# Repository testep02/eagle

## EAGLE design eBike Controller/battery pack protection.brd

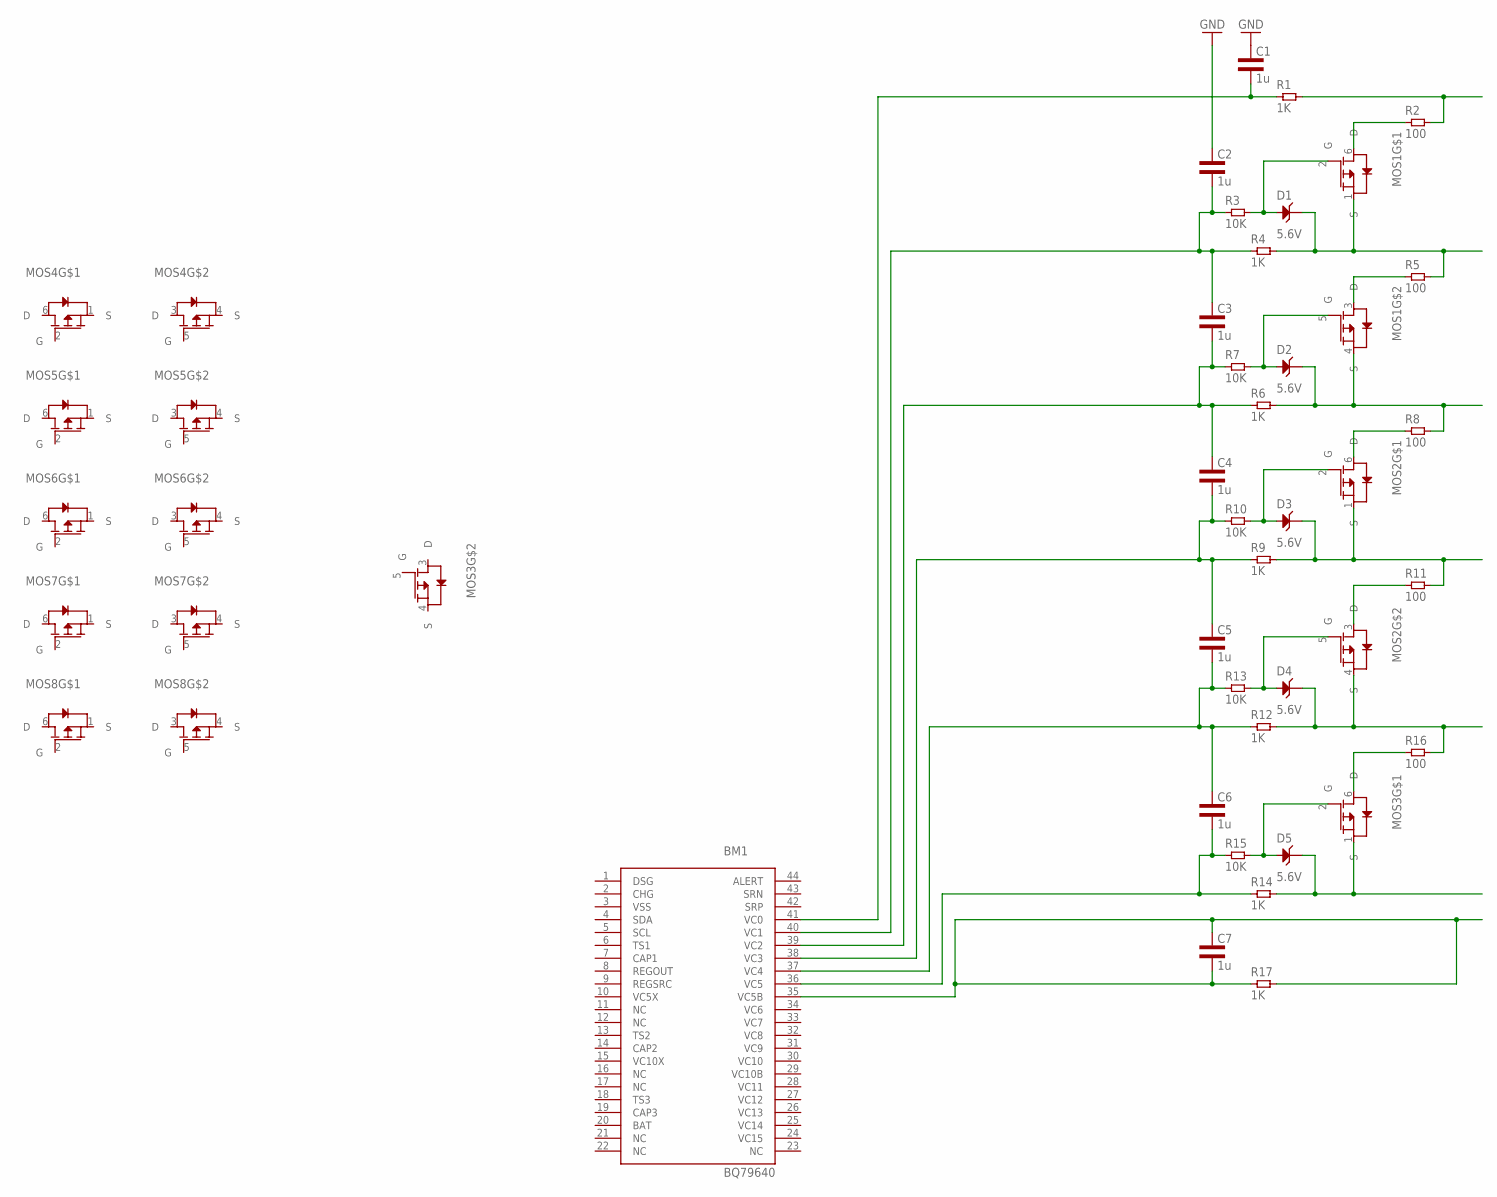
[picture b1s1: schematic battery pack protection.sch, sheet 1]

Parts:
BM1: BQ76940; R-PDSO-G44
C1, C2, C3, C4, C5, C6, C7: 1u; 0805L3
D1, D2, D3, D4, D5: 5.6V; SOD323
MOS1, MOS2, MOS3, MOS4, MOS5, MOS6, MOS7, MOS8: FDY1002PZ; SC89-6
R1, R4, R6, R9, R12, R14, R17: 1K; 0805L3
R2, R5, R8, R11, R16: 100; 1206L3
R3, R7, R10, R13, R15: 10K; 0805L3

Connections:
GND: C1.1, C2.1
unnamed: BM1.41 (VC0), C1.2, R1.1
unnamed: R1.2, R2.2
unnamed: MOS1.6 (D), R2.1
unnamed: D1.1 (ANODE), MOS1.2 (G), R3.2
unnamed: D1.2 (CATHODE), MOS1.1 (S), R4.2, R5.2
unnamed: BM1.40 (VC1), C2.2, C3.1, R3.1, R4.1
unnamed: D2.1 (ANODE), MOS1.5 (G), R7.2
unnamed: BM1.39 (VC2), C3.2, C4.1, R6.1, R7.1
unnamed: D2.2 (CATHODE), MOS1.4 (S), R6.2, R8.2
unnamed: MOS1.3 (D), R5.1
unnamed: BM1.38 (VC3), C4.2, C5.1, R9.1, R10.1
unnamed: D3.1 (ANODE), MOS2.2 (G), R10.2
unnamed: D3.2 (CATHODE), MOS2.1 (S), R9.2, R11.2
unnamed: MOS2.6 (D), R8.1
unnamed: BM1.37 (VC4), C5.2, C6.1, R12.1, R13.1
unnamed: D4.2 (CATHODE), MOS2.4 (S), R12.2, R16.2
unnamed: D4.1 (ANODE), MOS2.5 (G), R13.2
unnamed: MOS2.3 (D), R11.1
unnamed: BM1.36 (VC5), C6.2, R14.1, R15.1
unnamed: D5.2 (CATHODE), MOS3.1 (S), R14.2
unnamed: MOS3.6 (D), R16.1
unnamed: D5.1 (ANODE), MOS3.2 (G), R15.2
unnamed: BM1.35 (VC5B), C7.1, C7.2, R17.1, R17.2

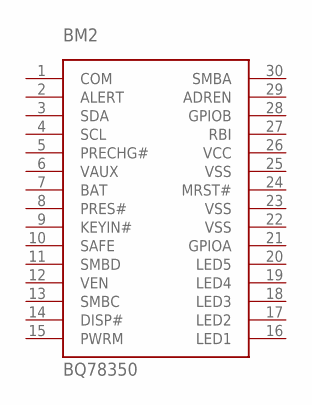
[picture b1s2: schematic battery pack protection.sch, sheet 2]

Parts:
BM2: BQ78350; R-PDSO-G30

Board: 4 copper layers, 39 parts (0 on the bottom side), 24 nets, no tracks yet.

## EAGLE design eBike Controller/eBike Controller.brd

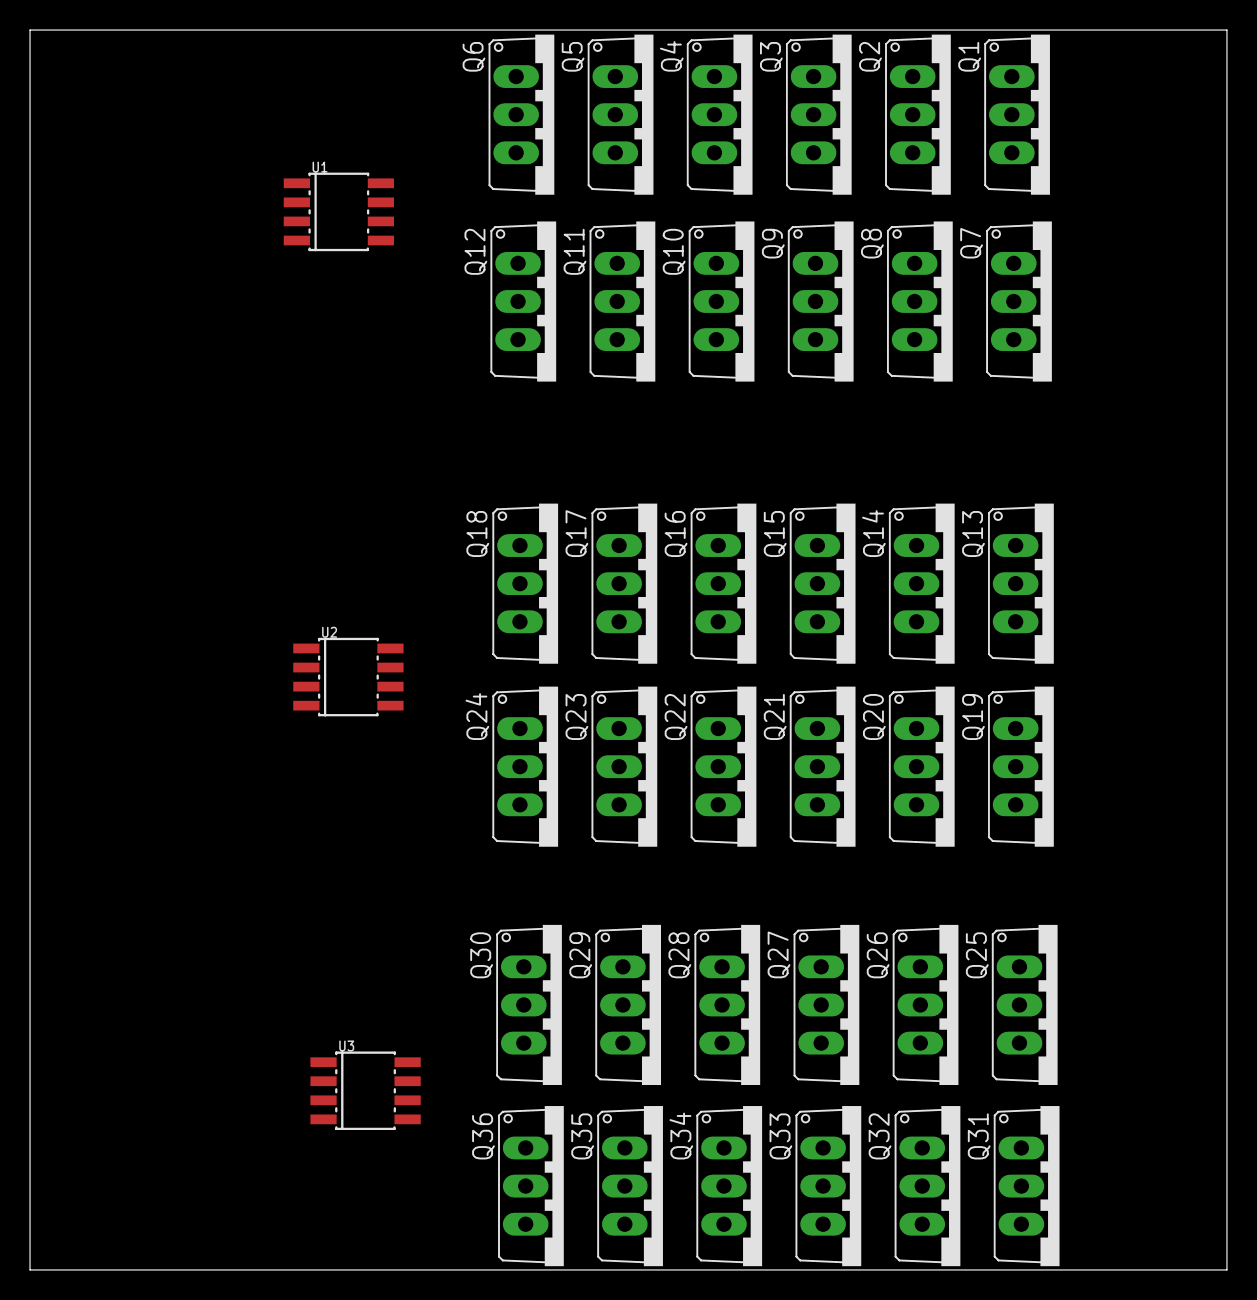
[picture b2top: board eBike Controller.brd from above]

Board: 2 copper layers, 79.7 x 82.6 mm, 39 parts (0 on the bottom side), 13 nets, no tracks yet.

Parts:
Q1, Q2, Q3, Q4, Q5, Q6, Q7, Q8, Q9, Q10, Q11, Q12, Q13, Q14, Q15, Q16, Q17, Q18, Q19, Q20, Q21, Q22, Q23, Q24, Q25, Q26, Q27, Q28, Q29, Q30, Q31, Q32, Q33, Q34, Q35, Q36: TO220V
U1, U2, U3: OPEN-BLDC_BD_IR2101; OPEN-BLDC_SO8

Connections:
BAT+: Q1.2, Q2.2, Q3.2, Q4.2, Q5.2, Q6.2, Q13.2, Q14.2, Q15.2, Q16.2, Q17.2, Q18.2, Q25.2, Q26.2, Q27.2, Q28.2, Q29.2, Q30.2
unnamed: Q1.3, Q2.3, Q3.3, Q4.3, Q5.3, Q6.3, Q7.2, Q8.2, Q9.2, Q10.2, Q11.2, Q12.2
unnamed: Q7.3, Q8.3, Q9.3, Q10.3, Q11.3, Q12.3
unnamed: Q7.1, Q8.1, Q9.1, Q10.1, Q11.1, Q12.1, U1.5
unnamed: Q1.1, Q2.1, Q3.1, Q4.1, Q5.1, Q6.1, U1.7
unnamed: Q13.3, Q14.3, Q15.3, Q16.3, Q17.3, Q18.3, Q19.2, Q20.2, Q21.2, Q22.2, Q23.2, Q24.2
unnamed: Q13.1, Q14.1, Q15.1, Q16.1, Q17.1, Q18.1, U2.7
unnamed: Q19.1, Q20.1, Q21.1, Q22.1, Q23.1, Q24.1, U2.5
unnamed: Q25.1, Q26.1, Q27.1, Q28.1, Q29.1, Q30.1, U3.7
unnamed: Q31.1, Q32.1, Q33.1, Q34.1, Q35.1, Q36.1, U3.5
unnamed: Q19.3, Q20.3, Q21.3, Q22.3, Q23.3, Q24.3
unnamed: Q25.3, Q26.3, Q27.3, Q28.3, Q29.3, Q30.3, Q31.2, Q32.2, Q33.2, Q34.2, Q35.2, Q36.2
unnamed: Q31.3, Q32.3, Q33.3, Q34.3, Q35.3, Q36.3

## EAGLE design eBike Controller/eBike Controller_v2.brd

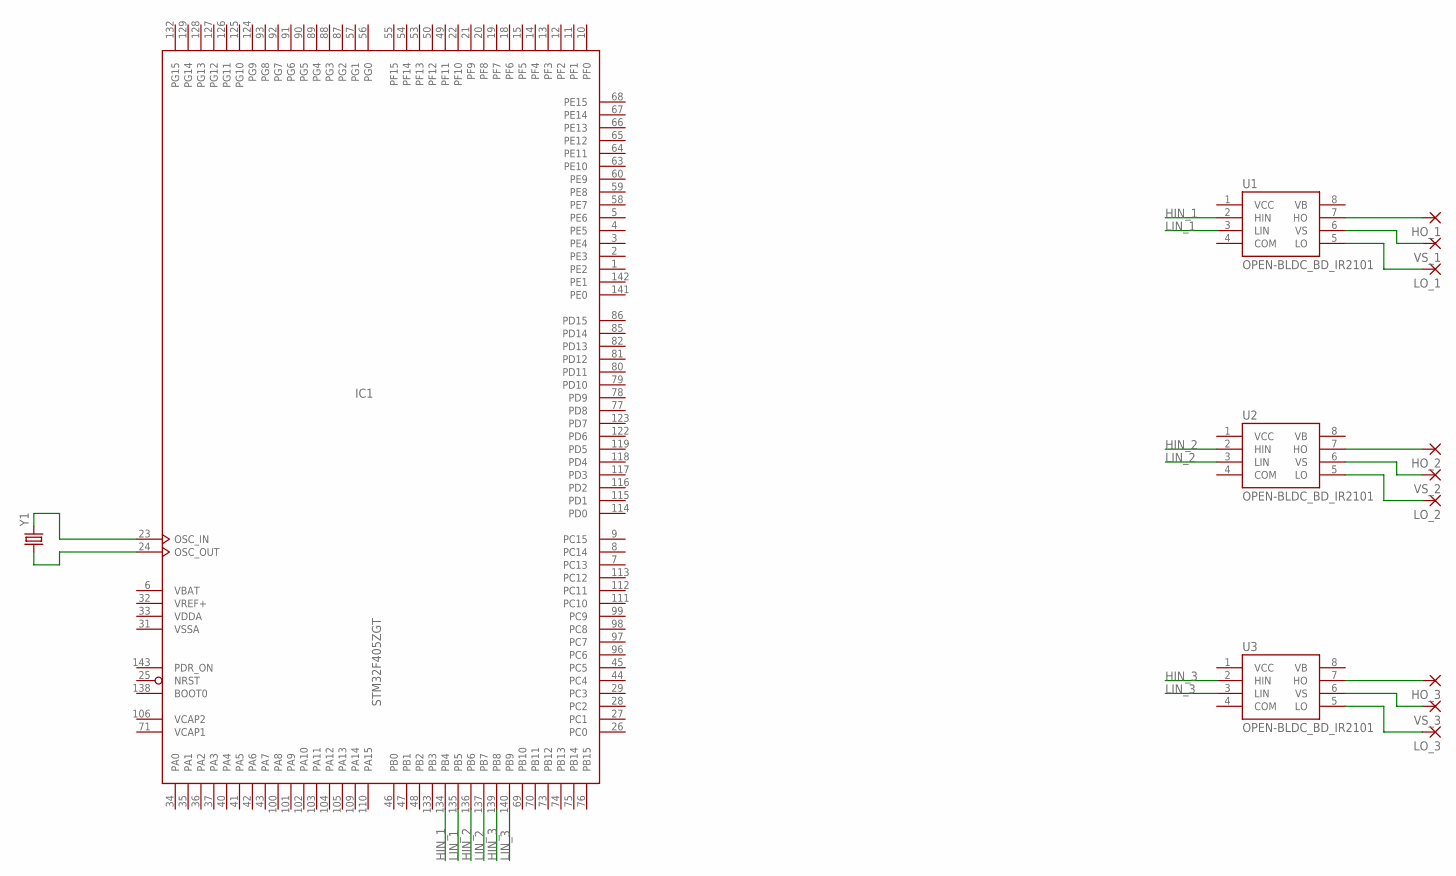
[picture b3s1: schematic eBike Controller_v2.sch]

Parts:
HO_1, HO_2, HO_3: 3,81/1,4
IC1: STM32F405ZGT; LQFP144
LO_1, LO_2, LO_3: 3,81/1,4
U1, U2, U3: OPEN-BLDC_BD_IR2101; OPEN-BLDC_SO8
VS_1, VS_2, VS_3: 3,81/1,4
Y1: CRYSTALHC49US; HC49US

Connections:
HIN_1: IC1.134 (PB4), U1.2 (HIN)
HIN_2: IC1.136 (PB6), U2.2 (HIN)
HIN_3: IC1.139 (PB8), U3.2 (HIN)
HO_1: HO_1.1, U1.7 (HO)
HO_2: HO_2.1, U2.7 (HO)
HO_3: HO_3.1, U3.7 (HO)
LIN_1: IC1.135 (PB5), U1.3 (LIN)
LIN_2: IC1.137 (PB7), U2.3 (LIN)
LIN_3: IC1.140 (PB9), U3.3 (LIN)
LO_1: LO_1.1, U1.5 (LO)
LO_2: LO_2.1, U2.5 (LO)
LO_3: LO_3.1, U3.5 (LO)
unnamed: IC1.24 (OSC_OUT), Y1.1
unnamed: IC1.23 (OSC_IN), Y1.2
VBAT: IC1.6 (VBAT)
VCAP1: IC1.71 (VCAP1)
VCAP2: IC1.106 (VCAP2)
VDD: IC1.17 (VDD), IC1.30 (VDD), IC1.39 (VDD), IC1.52 (VDD), IC1.62 (VDD), IC1.72 (VDD), IC1.84 (VDD), IC1.95 (VDD), IC1.108 (VDD), IC1.121 (VDD), IC1.131 (VDD), IC1.144 (VDD)
VDDA: IC1.33 (VDDA)
VREF+: IC1.32 (VREF+)
VSS: IC1.16 (VSS), IC1.38 (VSS), IC1.51 (VSS), IC1.61 (VSS), IC1.83 (VSS), IC1.94 (VSS), IC1.107 (VSS), IC1.120 (VSS), IC1.130 (VSS)
VSSA: IC1.31 (VSSA)
VS_1: U1.6 (VS), VS_1.1
VS_2: U2.6 (VS), VS_2.1
VS_3: U3.6 (VS), VS_3.1

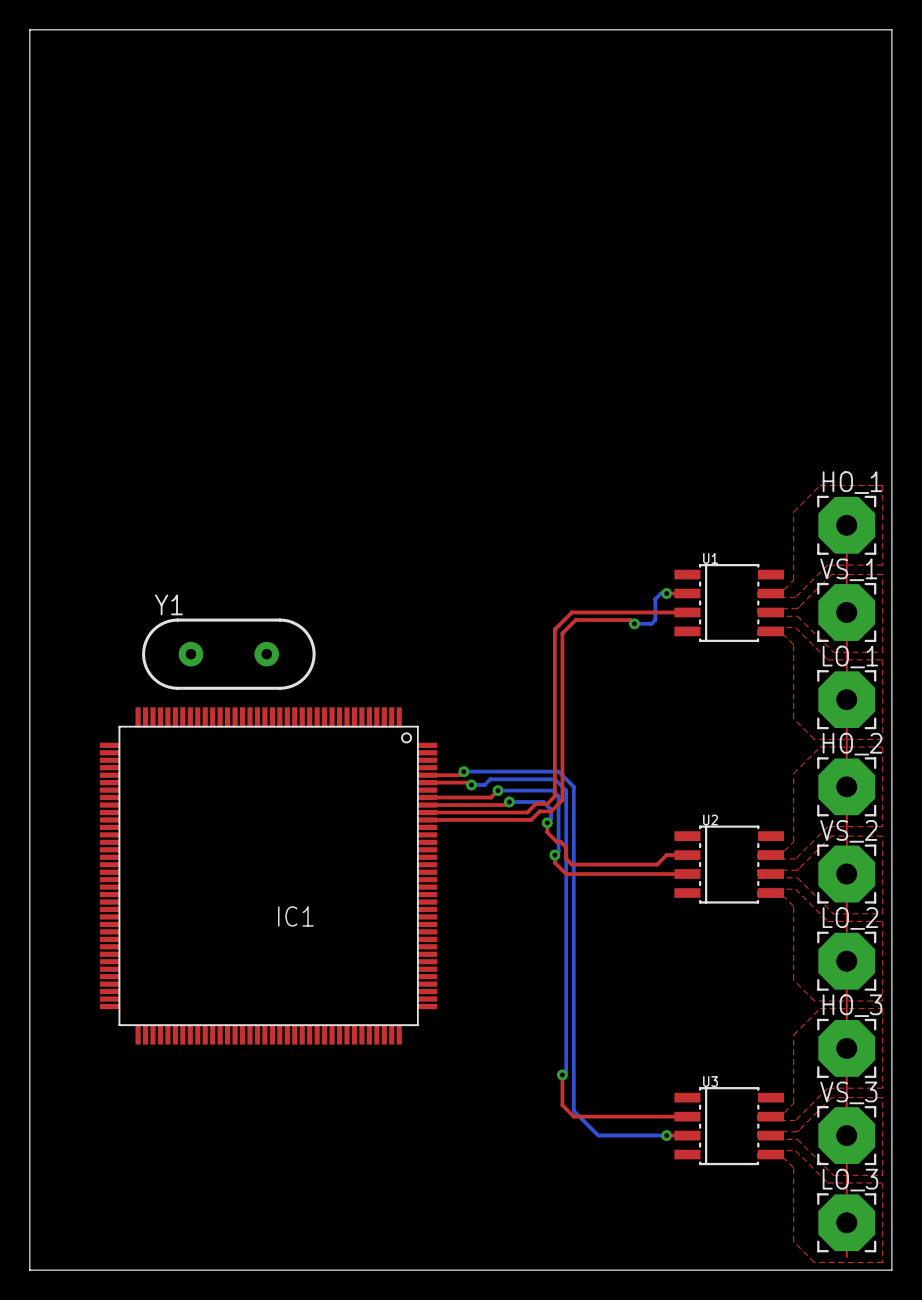
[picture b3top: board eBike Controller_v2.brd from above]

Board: 2 copper layers, 57.8 x 83.1 mm, 14 parts (0 on the bottom side), 19 nets.

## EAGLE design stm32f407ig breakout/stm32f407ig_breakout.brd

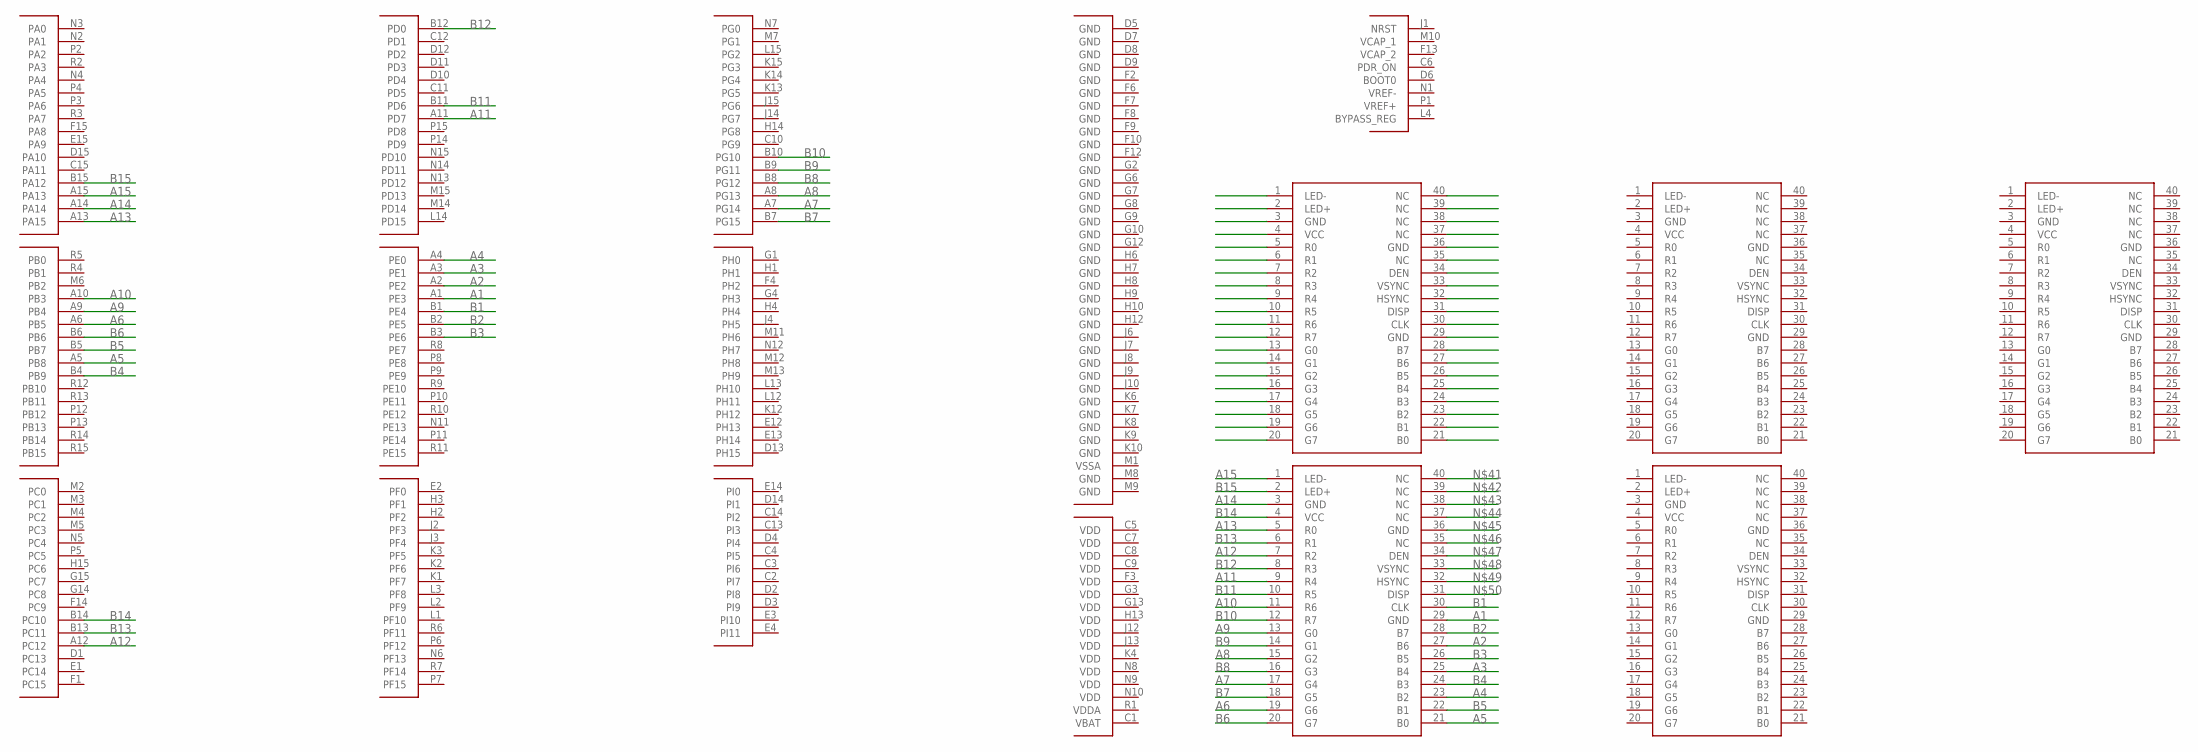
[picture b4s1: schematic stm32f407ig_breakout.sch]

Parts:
TFT1, TFT2, TFT3, TFT4, TFT5: MOLEX_CONNECTORS_SMD_NHD-4.3-480272EF-ATXL; MOLEX_CONNECTORS_SMD_40-PIN_SMD
U$1: STM32F407IG; UFBGA176+25

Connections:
A1: TFT4.29 (GND), U$1.A1 (PE3)
A2: TFT4.27 (B6), U$1.A2 (PE2)
A3: TFT4.25 (B4), U$1.A3 (PE1)
A4: TFT4.23 (B2), U$1.A4 (PE0)
A5: TFT4.21 (B0), U$1.A5 (PB8)
A6: TFT4.19 (G6), U$1.A6 (PB5)
A7: TFT4.17 (G4), U$1.A7 (PG14)
A8: TFT4.15 (G2), U$1.A8 (PG13)
A9: TFT4.13 (G0), U$1.A9 (PB4)
A10: TFT4.11 (R6), U$1.A10 (PB3)
A11: TFT4.9 (R4), U$1.A11 (PD7)
A12: TFT4.7 (R2), U$1.A12 (PC12)
A13: TFT4.5 (R0), U$1.A13 (PA15)
A14: TFT4.3 (GND), U$1.A14
A15: TFT4.1 (LED-), U$1.A15 (PA13)
B1: TFT4.30 (CLK), U$1.B1 (PE4)
B2: TFT4.28 (B7), U$1.B2 (PE5)
B3: TFT4.26 (B5), U$1.B3 (PE6)
B4: TFT4.24 (B3), U$1.B4 (PB9)
B5: TFT4.22 (B1), U$1.B5 (PB7)
B6: TFT4.20 (G7), U$1.B6
B7: TFT4.18 (G5), U$1.B7 (PG15)
B8: TFT4.16 (G3), U$1.B8 (PG12)
B9: TFT4.14 (G1), U$1.B9 (PG11)
B10: TFT4.12 (R7), U$1.B10 (PG10)
B11: TFT4.10 (R5), U$1.B11 (PD6)
B12: TFT4.8 (R3), U$1.B12 (PD0)
B13: TFT4.6 (R1), U$1.B13 (PC11)
B14: TFT4.4 (VCC), U$1.B14 (PC10)
B15: TFT4.2 (LED+), U$1.B15 (PA12)

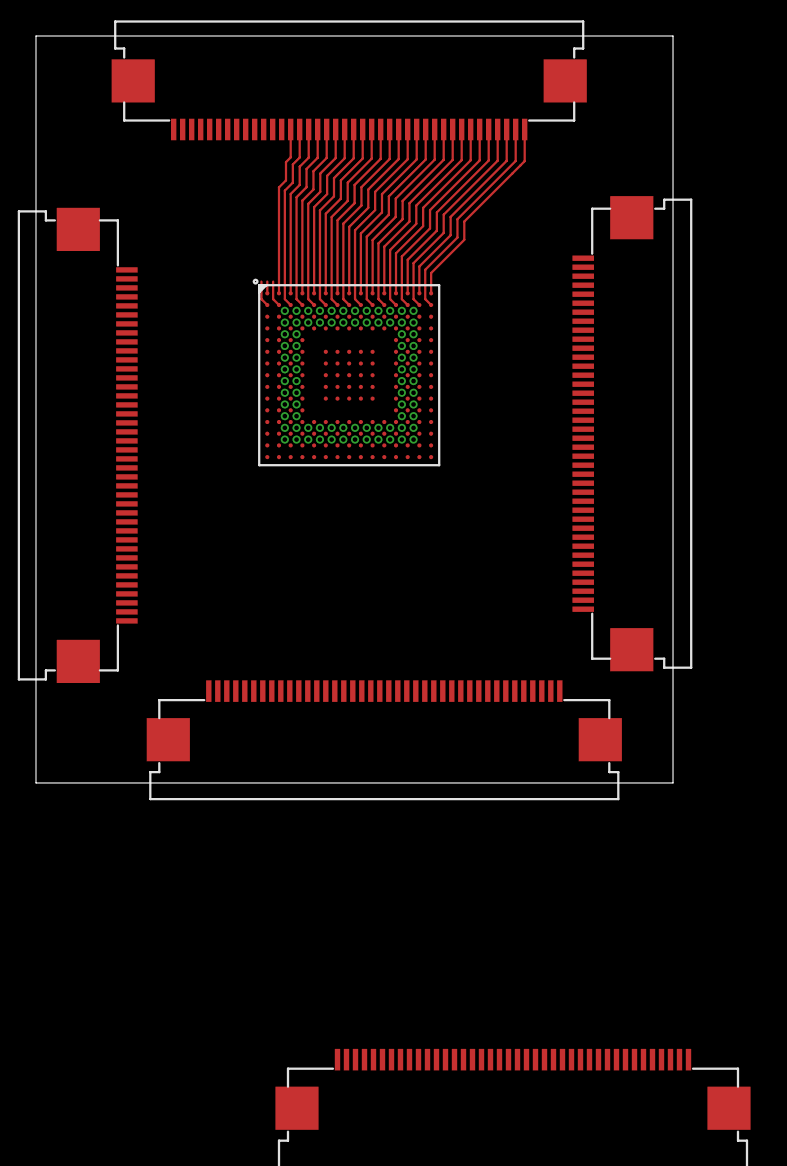
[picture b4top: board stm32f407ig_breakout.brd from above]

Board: 2 copper layers, 35.4 x 41.5 mm, 6 parts (0 on the bottom side), 30 nets.

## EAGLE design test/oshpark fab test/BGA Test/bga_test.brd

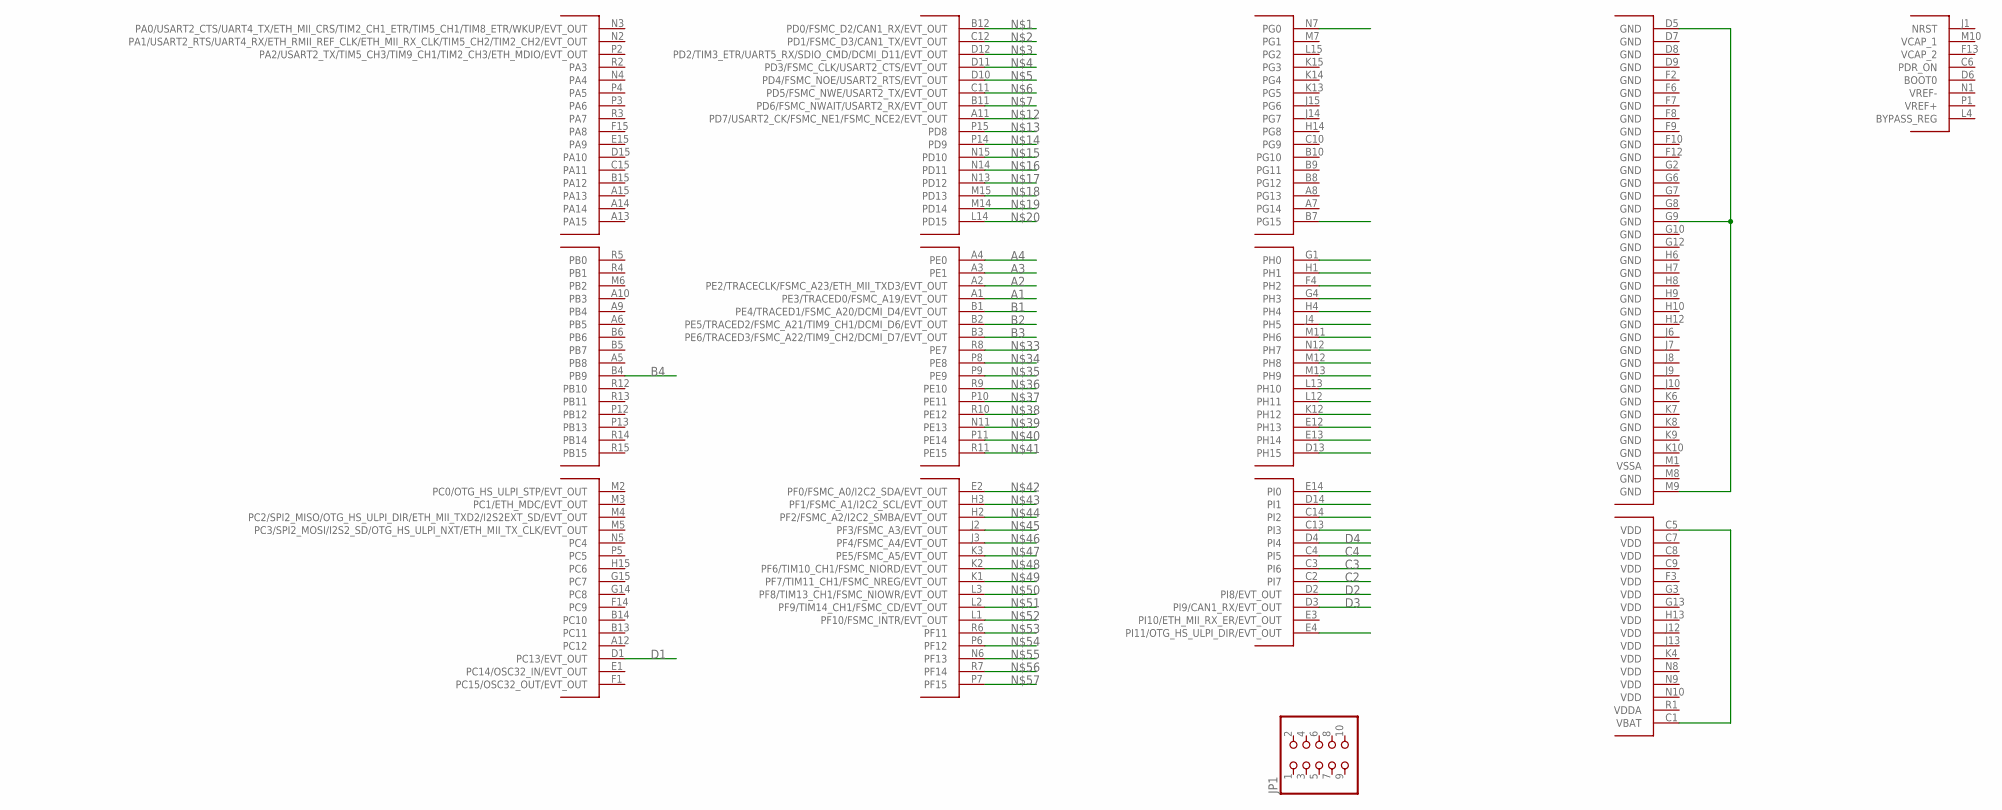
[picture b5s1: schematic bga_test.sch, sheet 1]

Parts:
JP1: PINHD-2X5; 2X05
U$1: STM32_32BIT_MCU_STM32F407IG; STM32_32BIT_MCU_UFBGA176+25

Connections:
A1: U$1.A1 (PE3/TRACED0/FSMC_A19/EVT_OUT); also elsewhere on the board
A2: U$1.A2 (PE2/TRACECLK/FSMC_A23/ETH_MII_TXD3/EVT_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); also elsewhere on the board
A3: U$1.A3 (PE1); also elsewhere on the board
A4: U$1.A4 (PE0); also elsewhere on the board
B1: U$1.B1 (PE4/TRACED1/FSMC_A20/DCMI_D4/EVT_OUT); also elsewhere on the board
B2: U$1.B2 (PE5/TRACED2/FSMC_A21/TIM9_CH1/DCMI_D6/E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); also elsewhere on the board
B3: U$1.B3 (PE6/TRACED3/FSMC_A22/TIM9_CH2/DCMI_D7/E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); also elsewhere on the board
B4: U$1.B4 (PB9); also elsewhere on the board
C2: U$1.C2 (PI7); also elsewhere on the board
C3: U$1.C3 (PI6); also elsewhere on the board
C4: U$1.C4 (PI5); also elsewhere on the board
D1: U$1.D1 (PC13/EVT_OUT)
D2: U$1.D2 (PI8/EVT_OUT); also elsewhere on the board
D3: U$1.D3 (PI9/CAN1_RX/EVT_OUT); also elsewhere on the board
D4: U$1.D4 (PI4); also elsewhere on the board
unnamed: U$1.D5 (GND), U$1.G9 (GND), U$1.M9 (GND)
unnamed: U$1.C1 (VBAT), U$1.C5 (VDD)

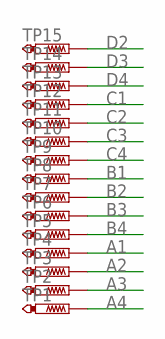
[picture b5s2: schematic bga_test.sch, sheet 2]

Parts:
TP1, TP2, TP3, TP4, TP5, TP6, TP7, TP8, TP9, TP10, TP11, TP12, TP13, TP14, TP15: PTR1TP06R; TP06R

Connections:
A1: TP4.TP; also elsewhere on the board
A2: TP3.TP; also elsewhere on the board
A3: TP2.TP; also elsewhere on the board
A4: TP1.TP; also elsewhere on the board
B1: TP8.TP; also elsewhere on the board
B2: TP7.TP; also elsewhere on the board
B3: TP6.TP; also elsewhere on the board
B4: TP5.TP; also elsewhere on the board
C1: TP12.TP
C2: TP11.TP; also elsewhere on the board
C3: TP10.TP; also elsewhere on the board
C4: TP9.TP; also elsewhere on the board
D2: TP15.TP; also elsewhere on the board
D3: TP14.TP; also elsewhere on the board
D4: TP13.TP; also elsewhere on the board

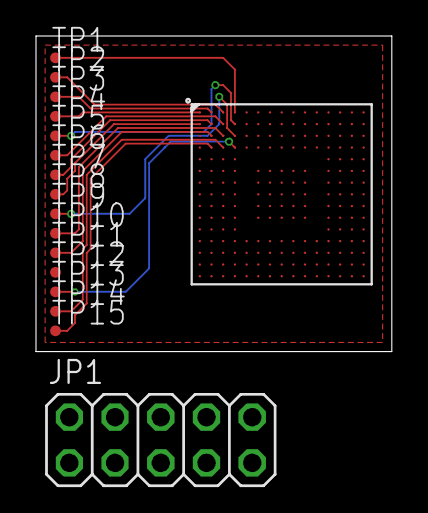
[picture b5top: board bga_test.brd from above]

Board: 4 copper layers, 19.8 x 17.5 mm, 17 parts (0 on the bottom side), 16 nets.

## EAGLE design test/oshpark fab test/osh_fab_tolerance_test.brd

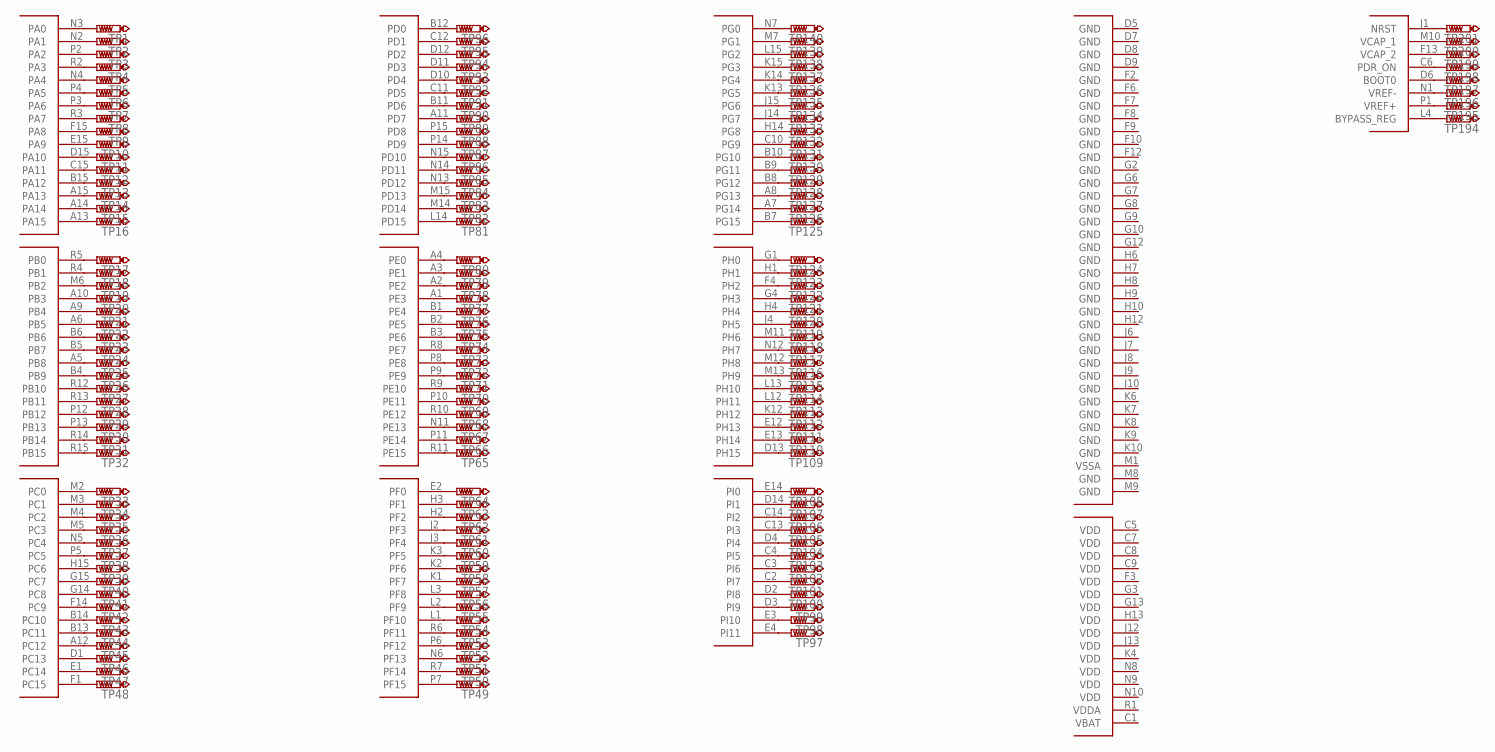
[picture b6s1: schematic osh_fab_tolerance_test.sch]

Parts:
TP1, TP2, TP3, TP4, TP5, TP6, TP7, TP8, TP9, TP10, TP11, TP12, TP13, TP14, TP15, TP16, TP17, TP18, TP19, TP20, TP21, TP22, TP23, TP24, TP25, TP26, TP27, TP28, TP29, TP30, TP31, TP32, TP33, TP34, TP35, TP36, TP37, TP38, TP39, TP40, TP41, TP42, TP43, TP44, TP45, TP46, TP47, TP48, TP49, TP50, TP51, TP52, TP53, TP54, TP55, TP56, TP57, TP58, TP59, TP60, TP61, TP62, TP63, TP64, TP65, TP66, TP67, TP68, TP69, TP70, TP71, TP72, TP73, TP74, TP75, TP76, TP77, TP78, TP79, TP80, TP81, TP82, TP83, TP84, TP85, TP86, TP87, TP88, TP89, TP90, TP91, TP92, TP93, TP94, TP95, TP96, TP97, TP98, TP99, TP100, TP101, TP102, TP103, TP104, TP105, TP106, TP107, TP108, TP109, TP110, TP111, TP112, TP113, TP114, TP115, TP116, TP117, TP118, TP119, TP120, TP121, TP122, TP123, TP124, TP125, TP126, TP127, TP128, TP129, TP130, TP131, TP132, TP133, TP134, TP135, TP136, TP137, TP138, TP139, TP140, TP194, TP195, TP196, TP197, TP198, TP199, TP200, TP201: PTR1TP09R; TP09R
U$1: STM32_32BIT_MCU_STM32F407IG; STM32_32BIT_MCU_UFBGA176+25

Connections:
unnamed: TP1.TP, U$1.N3 (PA0)
unnamed: TP2.TP, U$1.N2 (PA1)
unnamed: TP3.TP, U$1.P2 (PA2)
unnamed: TP4.TP, U$1.R2 (PA3)
unnamed: TP5.TP, U$1.N4 (PA4)
unnamed: TP6.TP, U$1.P4 (PA5)
unnamed: TP7.TP, U$1.P3 (PA6)
unnamed: TP8.TP, U$1.R3 (PA7)
unnamed: TP9.TP, U$1.F15 (PA8)
unnamed: TP10.TP, U$1.E15 (PA9)
unnamed: TP11.TP, U$1.D15 (PA10)
unnamed: TP12.TP, U$1.C15 (PA11)
unnamed: TP13.TP, U$1.B15 (PA12)
unnamed: TP14.TP, U$1.A15 (PA13)
unnamed: TP15.TP, U$1.A14
unnamed: TP16.TP, U$1.A13 (PA15)
unnamed: TP17.TP, U$1.R5 (PB0)
unnamed: TP18.TP, U$1.R4 (PB1)
unnamed: TP19.TP, U$1.M6 (PB2)
unnamed: TP20.TP, U$1.A10 (PB3)
unnamed: TP21.TP, U$1.A9 (PB4)
unnamed: TP22.TP, U$1.A6 (PB5)
unnamed: TP23.TP, U$1.B6
unnamed: TP24.TP, U$1.B5 (PB7)
unnamed: TP25.TP, U$1.A5 (PB8)
unnamed: TP26.TP, U$1.B4 (PB9)
unnamed: TP27.TP, U$1.R12 (PB10)
unnamed: TP28.TP, U$1.R13 (PB11)
unnamed: TP29.TP, U$1.P12 (PB12)
unnamed: TP30.TP, U$1.P13 (PB13)
unnamed: TP31.TP, U$1.R14 (PB14)
unnamed: TP32.TP, U$1.R15 (PB15)
unnamed: TP33.TP, U$1.M2 (PC0)
unnamed: TP34.TP, U$1.M3 (PC1)
unnamed: TP35.TP, U$1.M4 (PC2)
unnamed: TP36.TP, U$1.M5 (PC3)
unnamed: TP37.TP, U$1.N5 (PC4)
unnamed: TP38.TP, U$1.P5 (PC5)
unnamed: TP39.TP, U$1.H15 (PC6)
unnamed: TP40.TP, U$1.G15 (PC7)
unnamed: TP41.TP, U$1.G14 (PC8)
unnamed: TP42.TP, U$1.F14 (PC9)
unnamed: TP43.TP, U$1.B14 (PC10)
unnamed: TP44.TP, U$1.B13 (PC11)
unnamed: TP45.TP, U$1.A12 (PC12)
unnamed: TP46.TP, U$1.D1 (PC13)
unnamed: TP47.TP, U$1.E1 (PC14)
unnamed: TP48.TP, U$1.F1 (PC15)
unnamed: TP49.TP, U$1.P7 (PF15)
unnamed: TP50.TP, U$1.R7 (PF14)
unnamed: TP51.TP, U$1.N6 (PF13)
unnamed: TP52.TP, U$1.P6 (PF12)
unnamed: TP53.TP, U$1.R6 (PF11)
unnamed: TP54.TP, U$1.L1 (PF10)
unnamed: TP55.TP, U$1.L2 (PF9)
unnamed: TP56.TP, U$1.L3 (PF8)
unnamed: TP57.TP, U$1.K1 (PF7)
unnamed: TP58.TP, U$1.K2 (PF6)
unnamed: TP59.TP, U$1.K3 (PF5)
unnamed: TP60.TP, U$1.J3 (PF4)
unnamed: TP61.TP, U$1.J2 (PF3)
unnamed: TP62.TP, U$1.H2 (PF2)
unnamed: TP63.TP, U$1.H3 (PF1)
unnamed: TP64.TP, U$1.E2 (PF0)
unnamed: TP65.TP, U$1.R11 (PE15)
unnamed: TP66.TP, U$1.P11 (PE14)
unnamed: TP67.TP, U$1.N11 (PE13)
unnamed: TP68.TP, U$1.R10 (PE12)
unnamed: TP69.TP, U$1.P10 (PE11)
unnamed: TP70.TP, U$1.R9 (PE10)
unnamed: TP71.TP, U$1.P9 (PE9)
unnamed: TP72.TP, U$1.P8 (PE8)
unnamed: TP73.TP, U$1.R8 (PE7)
unnamed: TP74.TP, U$1.B3 (PE6)
unnamed: TP75.TP, U$1.B2 (PE5)
unnamed: TP76.TP, U$1.B1 (PE4)
unnamed: TP77.TP, U$1.A1 (PE3)
unnamed: TP78.TP, U$1.A2 (PE2)
unnamed: TP79.TP, U$1.A3 (PE1)
unnamed: TP80.TP, U$1.A4 (PE0)
unnamed: TP81.TP, U$1.L14 (PD15)
unnamed: TP82.TP, U$1.M14 (PD14)
unnamed: TP83.TP, U$1.M15 (PD13)
unnamed: TP84.TP, U$1.N13 (PD12)
unnamed: TP85.TP, U$1.N14 (PD11)
unnamed: TP86.TP, U$1.N15 (PD10)
unnamed: TP87.TP, U$1.P14 (PD9)
unnamed: TP88.TP, U$1.P15 (PD8)
unnamed: TP89.TP, U$1.A11 (PD7)
unnamed: TP90.TP, U$1.B11 (PD6)
unnamed: TP91.TP, U$1.C11 (PD5)
unnamed: TP92.TP, U$1.D10 (PD4)
unnamed: TP93.TP, U$1.D11 (PD3)
unnamed: TP94.TP, U$1.D12 (PD2)
unnamed: TP95.TP, U$1.C12 (PD1)
unnamed: TP96.TP, U$1.B12 (PD0)
unnamed: TP97.TP, U$1.E4 (PI11)
unnamed: TP98.TP, U$1.E3 (PI10)
unnamed: TP99.TP, U$1.D3 (PI9)
unnamed: TP100.TP, U$1.D2 (PI8)
unnamed: TP101.TP, U$1.C2 (PI7)
unnamed: TP102.TP, U$1.C3 (PI6)
unnamed: TP103.TP, U$1.C4 (PI5)
unnamed: TP104.TP, U$1.D4 (PI4)
unnamed: TP105.TP, U$1.C13 (PI3)
unnamed: TP106.TP, U$1.C14 (PI2)
unnamed: TP107.TP, U$1.D14 (PI1)
unnamed: TP108.TP, U$1.E14 (PI0)
unnamed: TP109.TP, U$1.D13 (PH15)
unnamed: TP110.TP, U$1.E13 (PH14)
unnamed: TP111.TP, U$1.E12 (PH13)
unnamed: TP112.TP, U$1.K12 (PH12)
unnamed: TP113.TP, U$1.L12 (PH11)
unnamed: TP114.TP, U$1.L13 (PH10)
unnamed: TP115.TP, U$1.M13 (PH9)
unnamed: TP116.TP, U$1.M12 (PH8)
unnamed: TP117.TP, U$1.N12 (PH7)
unnamed: TP118.TP, U$1.M11 (PH6)
unnamed: TP119.TP, U$1.J4 (PH5)
unnamed: TP120.TP, U$1.H4
unnamed: TP121.TP, U$1.G4 (PH3)
unnamed: TP122.TP, U$1.F4 (PH2)
unnamed: TP123.TP, U$1.H1
unnamed: TP124.TP, U$1.G1 (PH0)
unnamed: TP125.TP, U$1.B7 (PG15)
unnamed: TP126.TP, U$1.A7 (PG14)
unnamed: TP127.TP, U$1.A8 (PG13)
unnamed: TP128.TP, U$1.B8 (PG12)
unnamed: TP129.TP, U$1.B9 (PG11)
unnamed: TP130.TP, U$1.B10 (PG10)
unnamed: TP131.TP, U$1.C10 (PG9)
unnamed: TP132.TP, U$1.H14 (PG8)
unnamed: TP133.TP, U$1.J14 (PG7)
unnamed: TP134.TP, U$1.J15 (PG6)
unnamed: TP135.TP, U$1.K13 (PG5)
unnamed: TP136.TP, U$1.K14 (PG4)
unnamed: TP137.TP, U$1.K15 (PG3)
unnamed: TP138.TP, U$1.L15 (PG2)
unnamed: TP139.TP, U$1.M7 (PG1)
unnamed: TP140.TP, U$1.N7 (PG0)
unnamed: TP194.TP, U$1.L4 (BYPASS_REG)
unnamed: TP195.TP, U$1.P1 (VREF+)
unnamed: TP196.TP, U$1.N1 (VREF-)
unnamed: TP197.TP, U$1.D6 (BOOT0)
unnamed: TP198.TP, U$1.C6 (PDR_ON)
unnamed: TP199.TP, U$1.F13 (VCAP_2)
unnamed: TP200.TP, U$1.M10 (VCAP_1)
unnamed: TP201.TP, U$1.J1 (NRST)

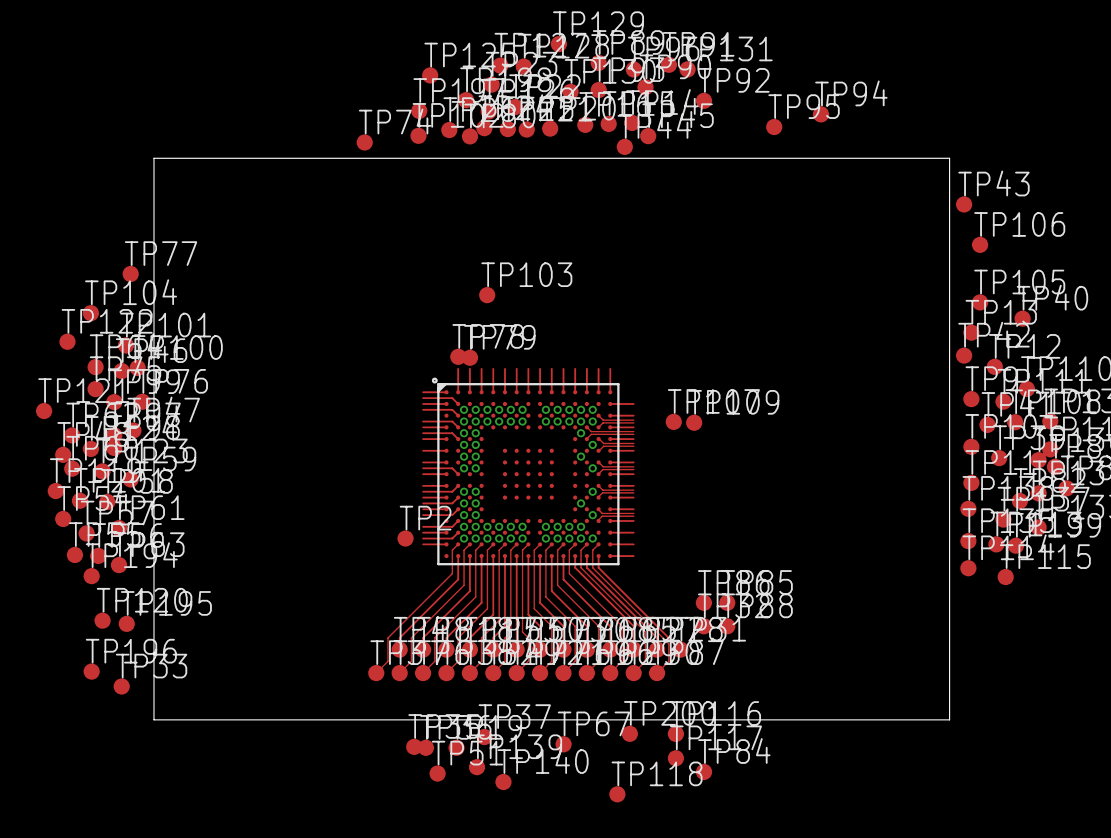
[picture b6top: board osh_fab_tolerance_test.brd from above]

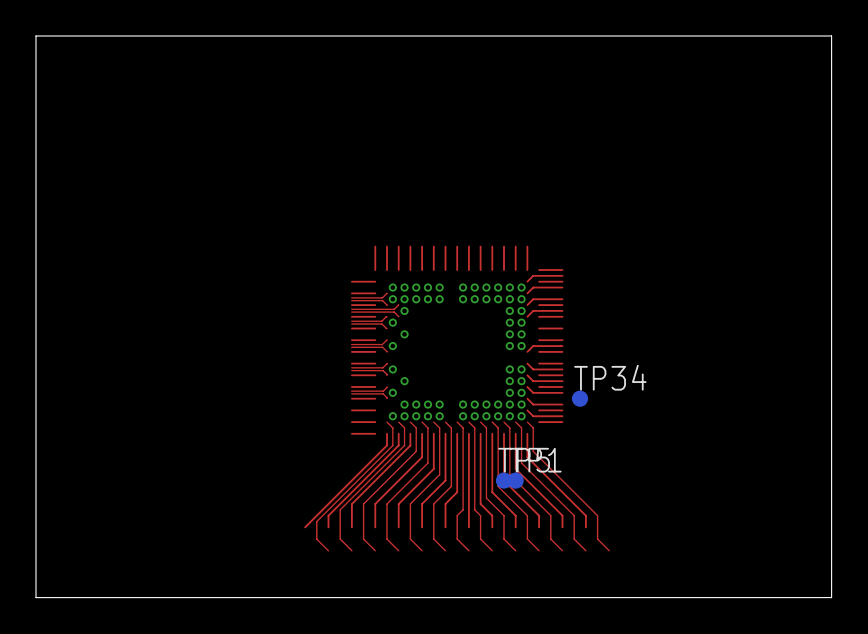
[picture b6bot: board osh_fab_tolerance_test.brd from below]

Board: 4 copper layers, 44.2 x 31.2 mm, 149 parts (3 on the bottom side), 148 nets.

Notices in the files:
parts and their libraries:
SparkFun-Aesthetics: Licensing: CC v3.0 Share-Alike You are welcome to use this library for commercial purposes.
